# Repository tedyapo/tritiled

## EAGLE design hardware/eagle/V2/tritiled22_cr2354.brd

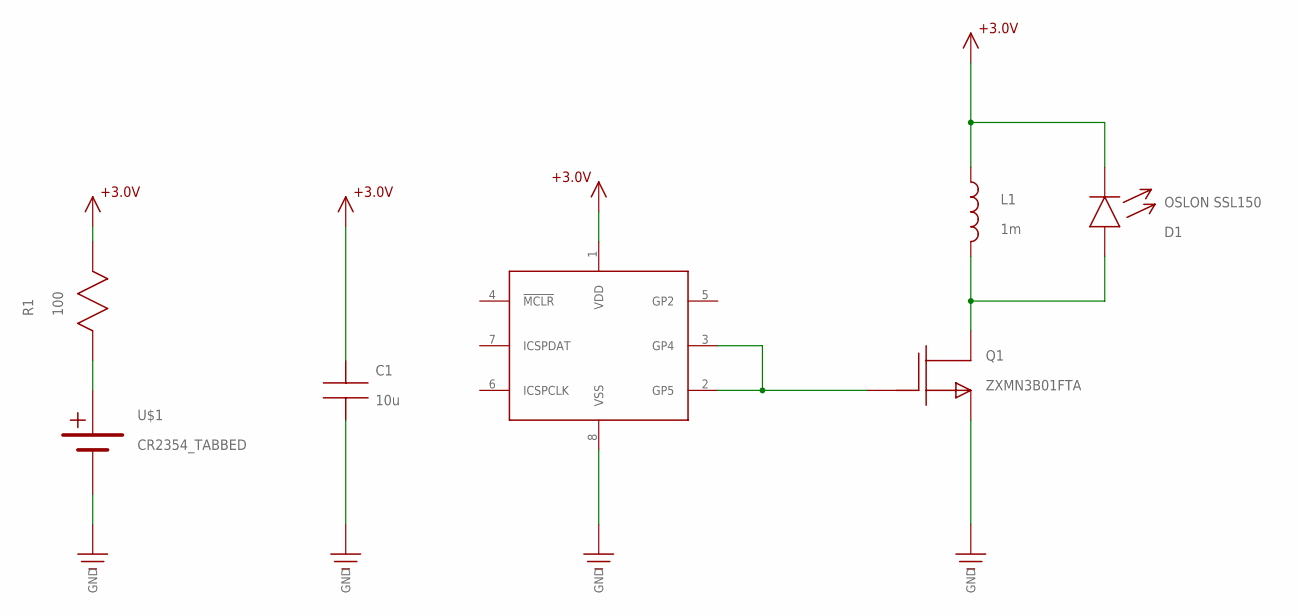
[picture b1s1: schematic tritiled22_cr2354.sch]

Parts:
C1: 10u; 1206
D1: OSLON SSL150; OSLON_3030_LED
L1: 1m; SRR6028_INDUCTOR
Q1: ZXMN3B01FTA; SOT-23
R1: 100; R1206
U1: PIC12LF1571; SOIC8
U$1: CR2354_TABBED

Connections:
+3.3V: C1.P$1, D1.C, L1.P$1 (1), R1.P$2, U1.1 (VDD)
GND: C1.P$2, Q1.2 (S), U1.8 (VSS), U$1.GND (0V)
unnamed: D1.A, L1.P$2 (2), Q1.3 (D)
unnamed: Q1.1 (G), U1.2 (GP5), U1.3 (GP4)
VBATT: R1.P$1, U$1.+3V (+V)

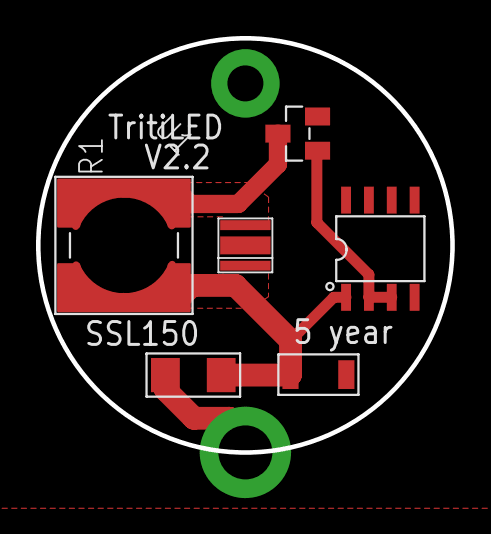
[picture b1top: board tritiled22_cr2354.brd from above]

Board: 2 copper layers, 23.0 x 23.0 mm, 7 parts (1 on the bottom side), 5 nets.

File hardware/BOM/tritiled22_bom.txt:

(1) PIC12LF1571 8-SOIC 
      DigiKey part # PIC12LF1571-I/SN-ND $0.57 each
(1) Wurth 744062102 1mH inductor
      DigiKey part # 732-3676-1-ND $1.57 each
(1) 10uF 25V 1206 X7R MLCC capacitor
      DigiKey part # 1276-1804-1-ND $0.26 each
(1) 0.1uF 25V 0805 X7R MLCC capacitor
      DigiKey part #311-1141-1-ND $0.10 each
(1) 100 ohm 1206 resistor
      DigiKey part # 311-100FRCT-ND $0.10 each
(1) ZXMN3B01FTA N-channel SOT23 MOSFET
      DigiKey part # ZXMN3B01FCT-ND $0.60 each
(1) DMG2305UX P-channel SOT23 MOSFET
      DigiKey part # DMG2305UX-13DICT-ND $0.44 each
(1) CR2032 Battery retainer
      Digikey part # BK-912-G-TR $0.63 each
(1) Switch E-Switch #TL3305BF260QG
      Digikey part # EG5354CT-ND $0.21 each
(1) CHANZON 3W LED (cyan is best).
    Find them on Amazon : $9.52/10, AliExpress : $7.90/10, or Ebay (various sellers/prices)
(1) PCB. Order from OSH Park. $6.15 for 3.

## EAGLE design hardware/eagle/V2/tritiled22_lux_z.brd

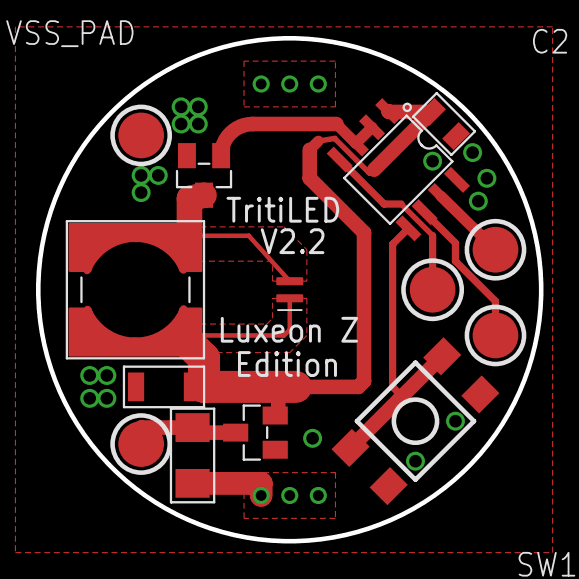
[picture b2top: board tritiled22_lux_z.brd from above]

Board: 2 copper layers, 27.9 x 27.9 mm, 15 parts (1 on the bottom side), 10 nets.

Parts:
B1: BAT-HLD-001_CR2032; CR2032_BAT-HLD_001
C1: 10u; 1206
C2: 100n; 0805
D1: Luxeon Z; LUXEON_Z
ICSPCLK_PAD: ICSP_PAD
ICSPDAT_PAD: ICSP_PAD
L1: 1m; SRR6028_INDUCTOR
MCLR_PAD: ICSP_PAD
Q1: ZXMN3B01FTA; SOT-23
Q2: DMG2305UX; SOT-23
R1: 100; R1206
SW1: SMD_SWITCH
U1: PIC12LF1571; SOIC8
VDD_PAD: ICSP_PAD
VSS_PAD: ICSP_PAD

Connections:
+3.3V: C1.P$1, C2.P$1, D1.C, L1.P$1, Q2.2, U1.1
GND: B1.GND, C1.P$2, C2.P$2, Q1.2, Q2.1, SW1.P$3, SW1.P$4, U1.8, VSS_PAD.P$2
unnamed: MCLR_PAD.P$2, U1.4
unnamed: ICSPDAT_PAD.P$2, U1.7
unnamed: ICSPCLK_PAD.P$2, U1.6
unnamed: D1.A, L1.P$2, Q1.3
unnamed: SW1.P$1, SW1.P$2, U1.5
unnamed: Q1.1, U1.2, U1.3
VBATT: B1.+V1, B1.+V2, R1.P$1
VSAFE: Q2.3, R1.P$2, VDD_PAD.P$2
